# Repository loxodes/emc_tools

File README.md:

# em_probes
experimental open hardware near field e-field and h-field probes

See doc folder for scalar network analyzer captures of probe performance.

h-field probe design from "Study of Magnetic Probes Used in EMI Measurements", DOI 10.1109/APEMC.2015.7175309

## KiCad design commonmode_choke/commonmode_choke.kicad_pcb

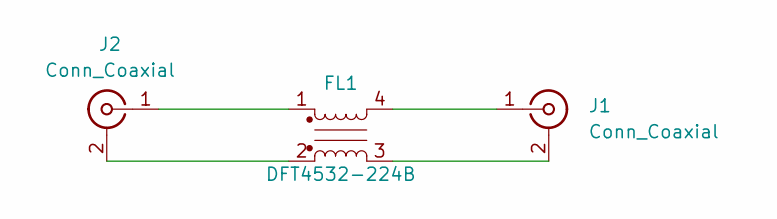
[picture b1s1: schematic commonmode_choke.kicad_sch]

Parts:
FL1: DFT4532-224B; DFT4532
J1, J2: Conn_Coaxial; SMA_Cinch_142-0711-821_EdgeMount

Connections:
unnamed: FL1.3, J1.2 (Ext)
unnamed: FL1.4, J1.1 (In)
unnamed: FL1.2, J2.2 (Ext)
unnamed: FL1.1, J2.1 (In)

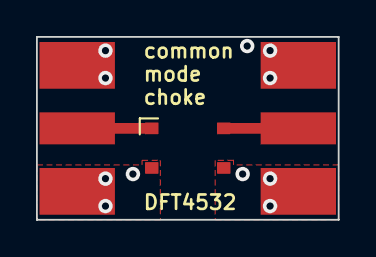
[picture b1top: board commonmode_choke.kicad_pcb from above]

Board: 2 copper layers, 16.8 x 10.2 mm, 3 parts (0 on the bottom side), 4 nets.

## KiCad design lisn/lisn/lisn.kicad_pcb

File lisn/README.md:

Line impedance stabilization network (LISN) for conducted emission testing, design based on 
http://www.eevblog.com/forum/projects/5uh-lisn-for-spectrum-analyzer-emcemi-work/msg404662/#msg404662

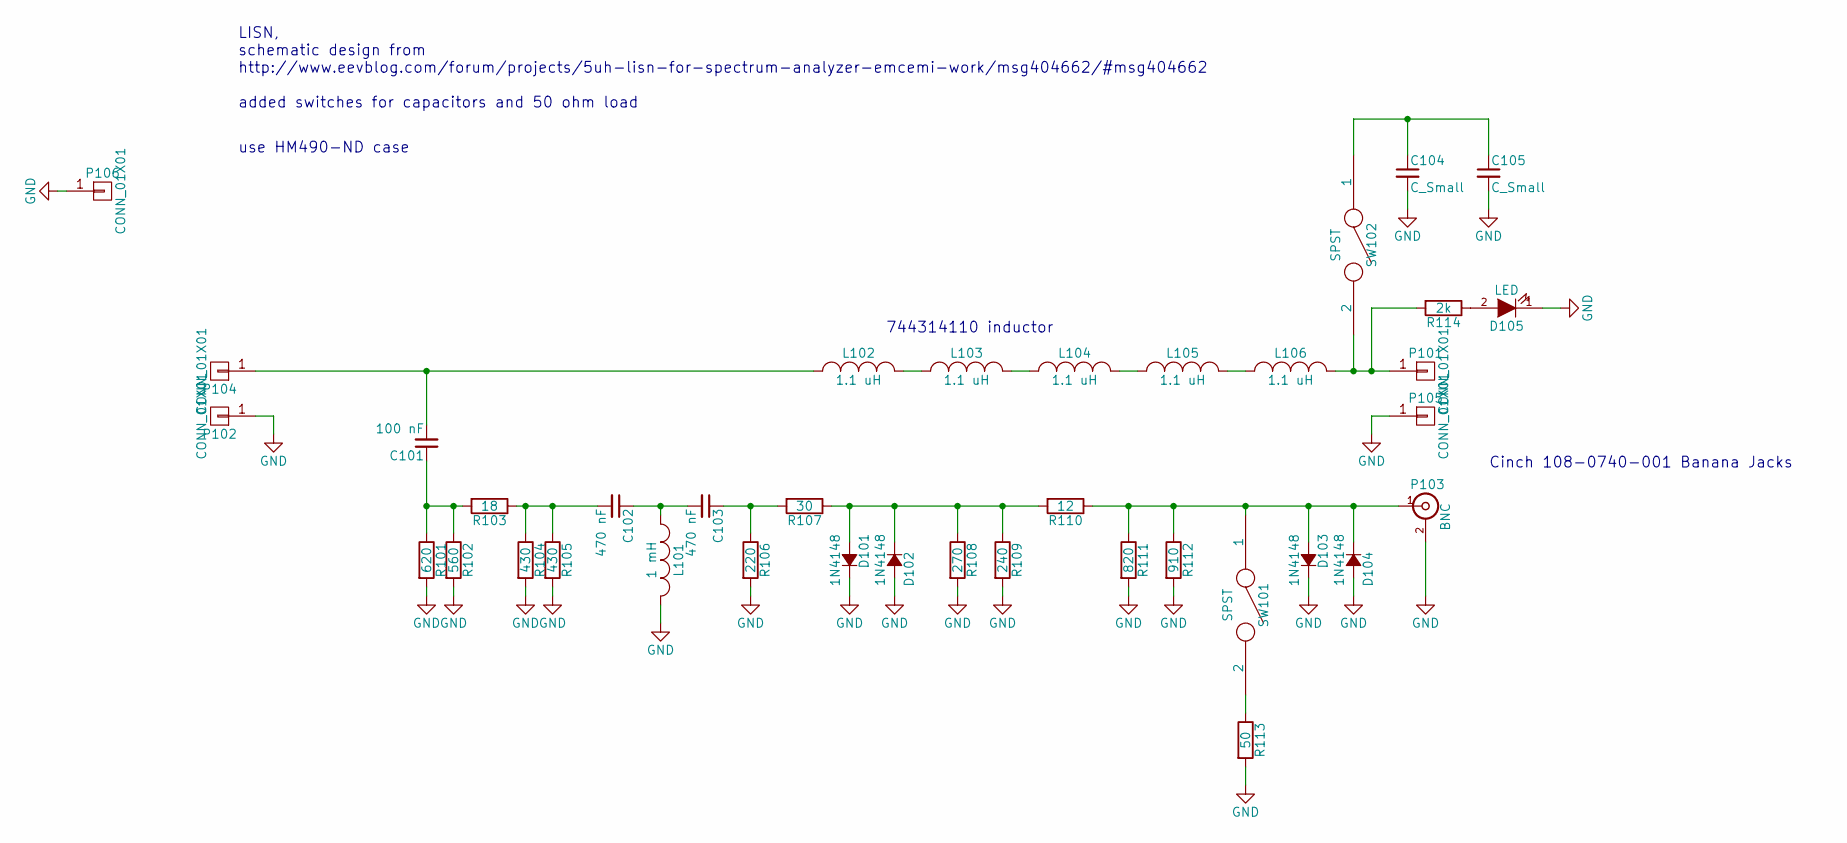
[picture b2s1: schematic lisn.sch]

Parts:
C101: 100 nF; C_1210
C102, C103: 470 nF; C_0805
C104: C_Small; C_0805
C105: C_Small; C_1210
D101, D102, D103, D104: 1N4148; SOD-123
D105: LED; LED_0603
L101: 1 mH; R_1210
L102, L103, L104, L105, L106: 1.1 uH; WE-HCI-7050
P101, P102, P104, P105: CONN_01X01; cinch_banana_jack
P103: BNC; bnc-ci
P106: CONN_01X01; 1590B
R101: 620; R_1210
R102: 560; R_1210
R103: 18; R_1210
R104, R105: 430; R_1210
R106: 220; R_1210
R107: 30; R_1210
R108: 270; R_0805
R109: 240; R_0805
R110: 12; R_0805
R111: 820; R_0805
R112: 910; R_0805
R113: 50; R_0805
R114: 2k; R_1210
SW101, SW102: SPST; SW_Micro_SPST

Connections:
GND: C104.2, C105.2, D101.1 (K), D102.2 (A), D103.1 (K), D104.2 (A), D105.1 (K), L101.2, P102.1, P103.2 (Ext), P105.1, P106.1, R101.2, R102.2, R104.2, R105.2, R106.2, R108.2, R109.2, R111.2, R112.2, R113.2
unnamed: C101.1, R101.1, R102.1, R103.2
unnamed: C101.2, L102.1, P104.1
unnamed: C102.1, C103.2, L101.1
unnamed: C102.2, R103.1, R104.1, R105.1
unnamed: C103.1, R106.1, R107.2
unnamed: C104.1, C105.1, SW102.1
unnamed: D101.2 (A), D102.1 (K), R107.1, R108.1, R109.1, R110.2
unnamed: D103.2 (A), D104.1 (K), P103.1 (In), R110.1, R111.1, R112.1, SW101.1
unnamed: D105.2 (A), R114.1
unnamed: L102.2, L103.1
unnamed: L103.2, L104.1
unnamed: L104.2, L105.1
unnamed: L105.2, L106.1
unnamed: L106.2, P101.1, R114.2, SW102.2
unnamed: R113.1, SW101.2

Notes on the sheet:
LISN, schematic design from http://www.eevblog.com/forum/projects/5uh-lisn-for-spectrum-analyzer-emcemi-work/msg404662/#msg404662 added switches for capacitors and 50 ohm load
744314110 inductor
use HM490-ND case
Cinch 108-0740-001 Banana Jacks

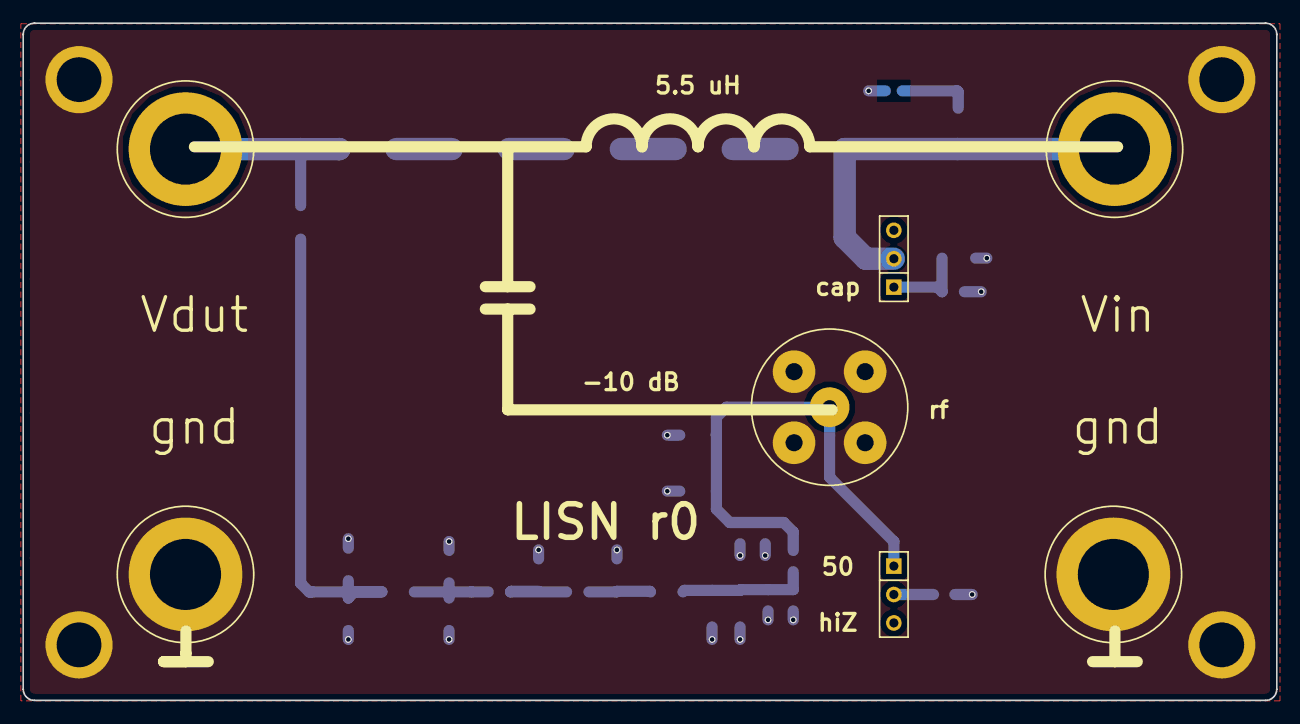
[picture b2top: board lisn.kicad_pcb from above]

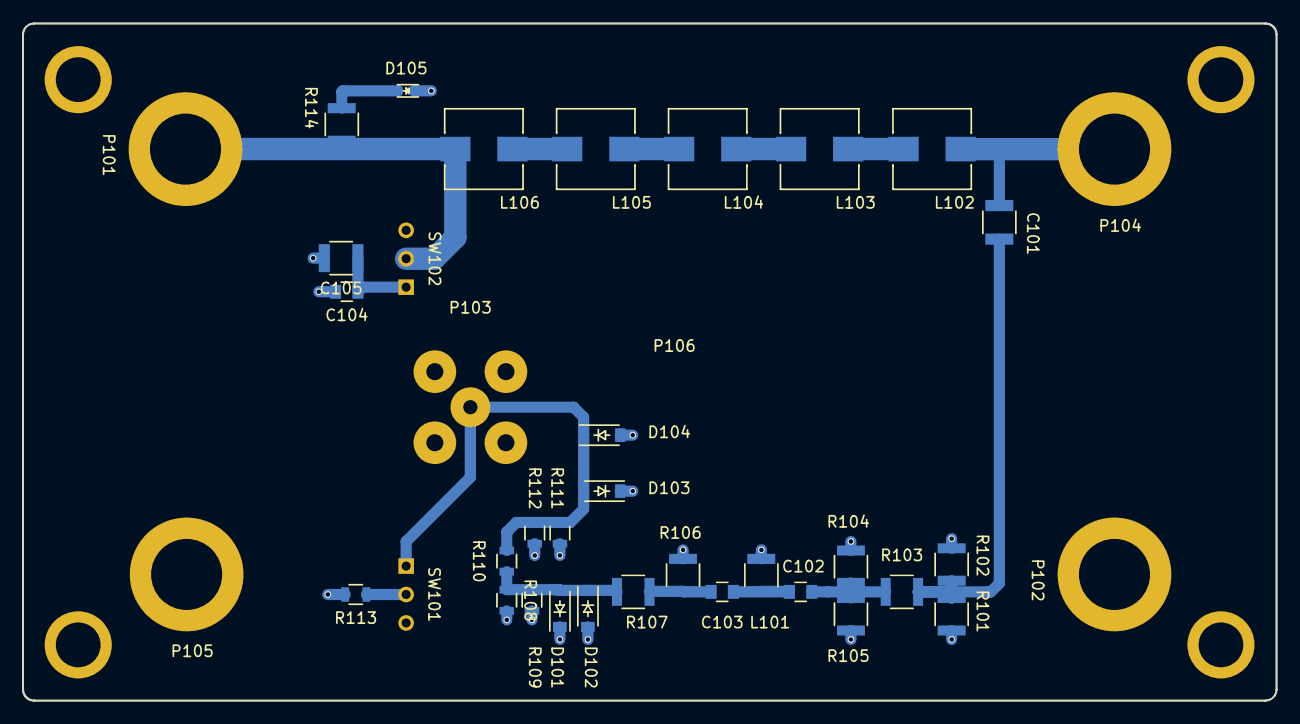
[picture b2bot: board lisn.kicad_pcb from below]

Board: 2 copper layers, 112.0 x 60.5 mm, 38 parts (31 on the bottom side), 16 nets.

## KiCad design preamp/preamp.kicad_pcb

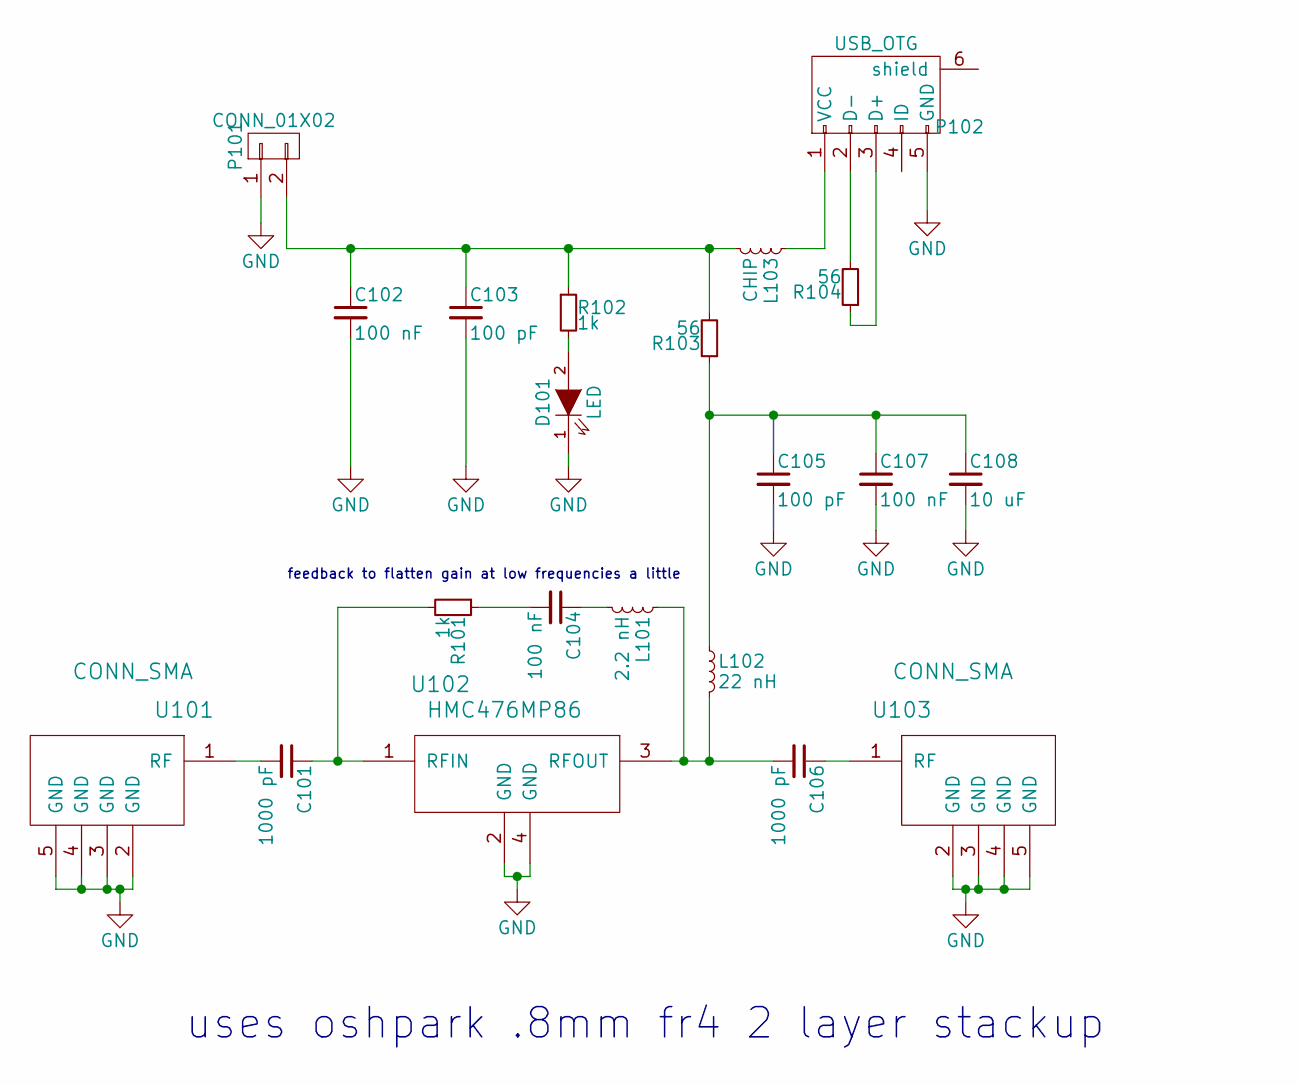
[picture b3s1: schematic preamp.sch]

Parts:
C101, C106: 1000 pF; C_0402
C102, C104, C107: 100 nF; C_0402
C103, C105: 100 pF; C_0402
C108: 10 uF; C_0603
D101: LED; LED_0603
L101: 2.2 nH; R_0402
L102: 22 nH; R_0402
L103: CHIP; R_0603
P101: CONN_01X02; Pin_Header_Straight_1x02
P102: USB_OTG; USB_Micro-B_10103594-0001LF
R101, R102: 1k; R_0402
R103, R104: 56; R_0402
U101, U103: CONN_SMA; 732512200_SMA
U102: HMC476MP86; sot86

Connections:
GND: C102.2, C103.2, C105.2, C107.2, C108.2, D101.1 (K), P101.1, P102.5 (GND), U101.2 (GND), U101.3 (GND), U101.4 (GND), U101.5 (GND), U102.2 (GND), U102.4 (GND), U103.2 (GND), U103.3 (GND), U103.4 (GND), U103.5 (GND)
unnamed: C101.1, R101.2, U102.1 (RFIN)
unnamed: C101.2, U101.1 (RF)
unnamed: C102.1, C103.1, L103.2, P101.2, R102.1, R103.2
unnamed: C104.1, L101.2
unnamed: C104.2, R101.1
unnamed: C105.1, C107.1, C108.1, L102.1, R103.1
unnamed: C106.1, U103.1 (RF)
unnamed: C106.2, L101.1, L102.2, U102.3 (RFOUT)
unnamed: D101.2 (A), R102.2
unnamed: L103.1, P102.1 (VCC)
unnamed: P102.2 (D-), R104.2
unnamed: P102.3 (D+), R104.1

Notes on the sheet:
feedback to flatten gain at low frequencies a little
uses oshpark .8mm fr4 2 layer stackup

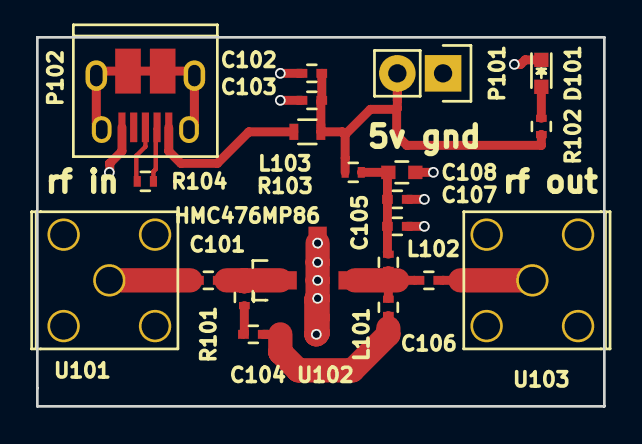
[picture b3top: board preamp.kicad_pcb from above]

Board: 2 copper layers, 31.5 x 20.5 mm, 21 parts (0 on the bottom side), 13 nets.

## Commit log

2016-05-17 added stripline test board
2016-05-18 added 5mm e field probe
2016-05-18 added h field probe
2016-05-18 added missing kicad libraries, updated documentation
2016-05-19 added preamplifier schematic for em probes
2016-05-19 finished component placement for preamp
2016-05-19 added layout for preamp
2016-06-04 Added measurements of probes
2016-06-04 fixed e probe measurements, added README for doc folder
2016-06-06 fixed typo in doc README
2016-06-07 added sweep of preamp without gain flattening feedback populated
2016-06-27 added 5.5 uH line impedance stabilization network
2016-09-28 added picture of lisn r1
2022-12-26 started common mode choke for pdn measurements with vna
